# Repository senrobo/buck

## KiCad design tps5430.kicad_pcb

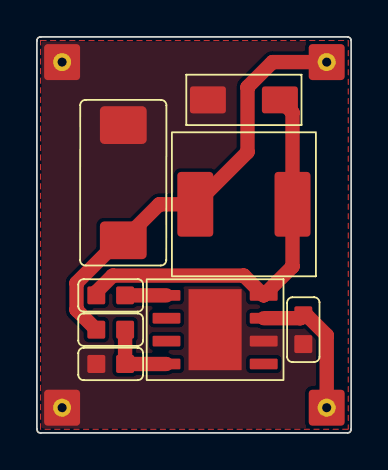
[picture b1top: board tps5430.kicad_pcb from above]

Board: 2 copper layers, 17.5 x 22.0 mm, 12 parts (0 on the bottom side), 6 nets.

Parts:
C1: 10n; cap0603
C2: 220u; EIA-7343-D
C3: 10u; cap0603
D1: SS54; DIOM5025X220N
J1, J2, J3, J4: Conn_01x01_Pin; 2x2mm Pad
L1: 15uH; 0630 One Piece Inductor
R1: 10K; res0603
R2: 3K24; res0603
U1: TPS5430DDA; TI_SO-PowerPAD-8_ThermalVias

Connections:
+5V: C2.1, J2.1, L1.2, R1.1
+12V: C3.1, J1.1, U1.7 (VIN)
GND: C2.2, C3.2, D1.2 (A), J3.1, J4.1, R2.2, U1.6 (GND), U1.9 (GNDPAD)
unnamed: C1.2, D1.1 (K), L1.1, U1.8 (PH)
unnamed: C1.1, U1.1 (BOOT)
unnamed: R1.2, R2.1, U1.4 (VSENSE)

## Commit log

2022-12-27 Ported from Altium 365
2023-05-19 kicad
2023-05-21 drc errors
2023-05-21 final
2023-05-22 done
2023-05-22 gerber
2023-05-23 jlcpcb
